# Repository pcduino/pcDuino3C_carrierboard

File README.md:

# pcDuino3C_carrierboard
This is the fully open source pcDuino3C carrierboard design files

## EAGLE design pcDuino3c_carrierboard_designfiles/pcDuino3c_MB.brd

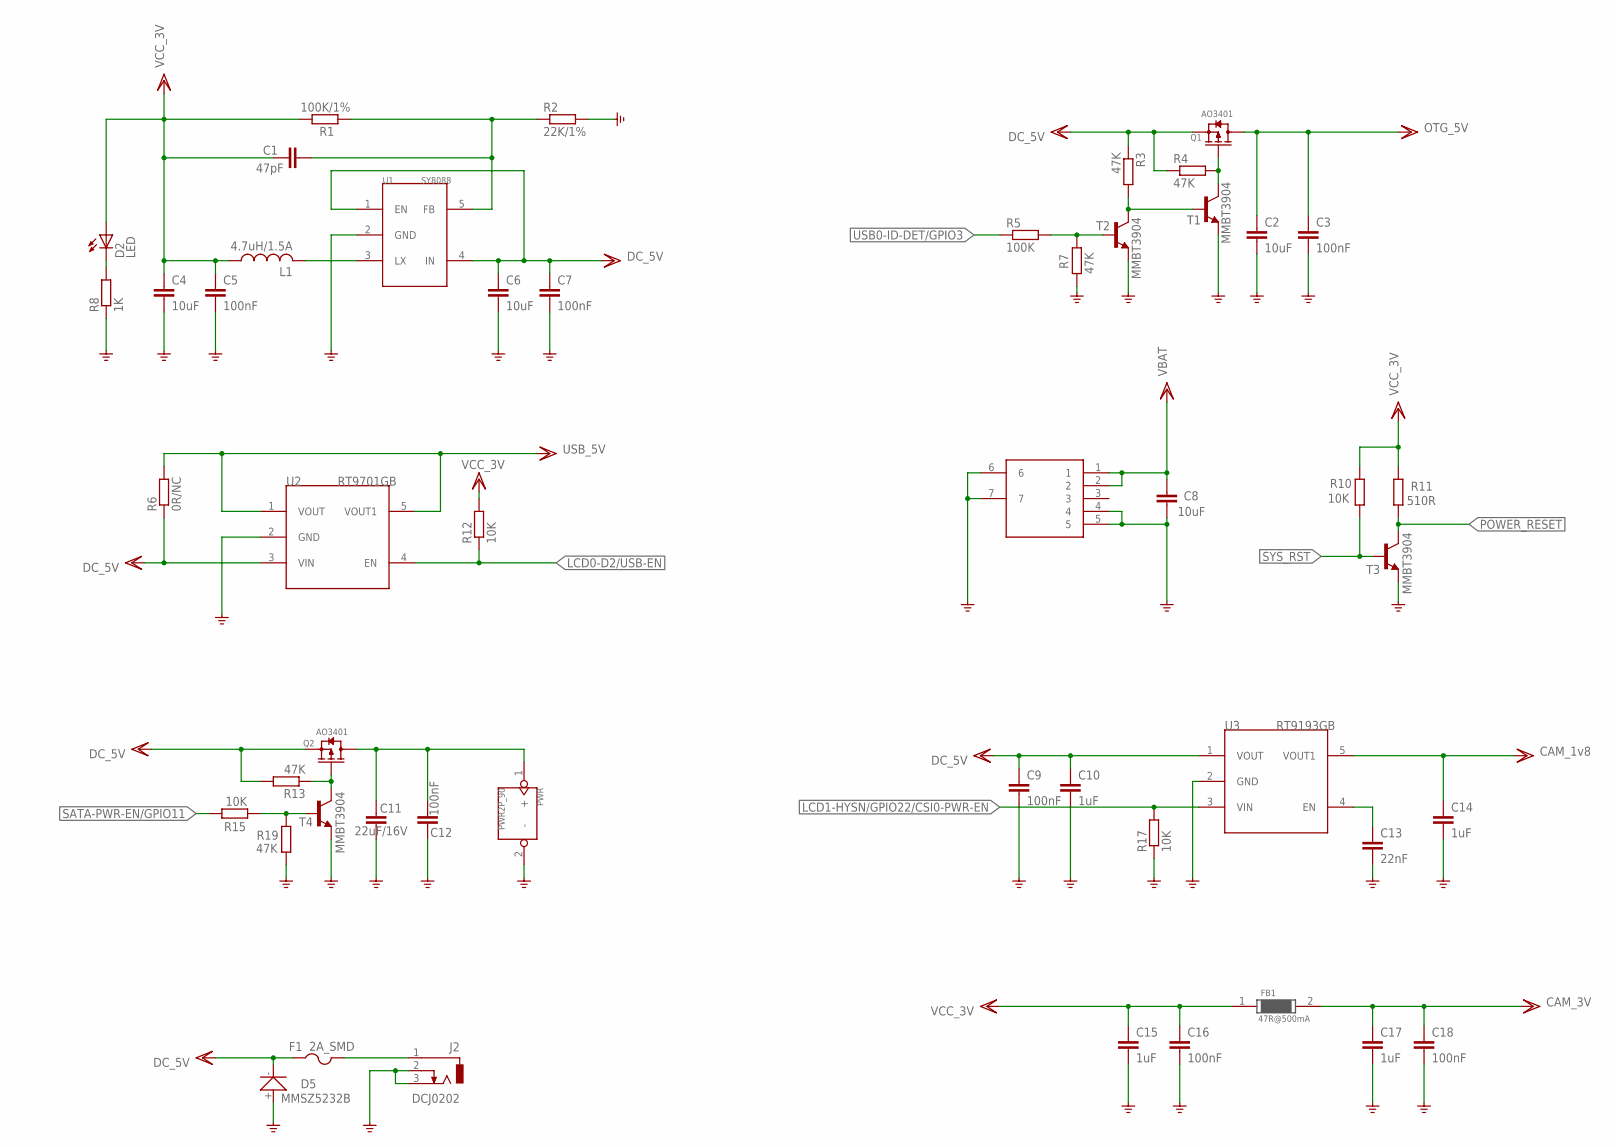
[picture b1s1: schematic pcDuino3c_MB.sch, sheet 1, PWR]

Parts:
C1: 47pF; C0402K
C2, C4, C6, C8: 10uF; C0805
C3, C5, C7, C12, C16, C18: 100nF; C0402K
C9: 100nF; C0805
C10, C14: 1uF; C0402K
C11: 22uF/16V; C0805
C13: 22nF; C0402K
C15, C17: 1uF; C0805
D2: LED; CHIP-LED-0805
D5: MMSZ5232B; SOD123
F1: 2A_SMD; R1206
FB1: 47R@500mA; R0603
J1: CON-BAT; CON-BAT-5P-1MM
J2: DCJ0202
L1: 4.7uH/1.5A; L_CD32
PWR: PWR2P_90; PWR2P_2.54
Q1, Q2: AO3401; SOT23
R1: 100K/1%; R0402
R2: 22K/1%; R0402
R3, R4, R7, R13, R19: 47K; R0402
R5: 100K; R0402
R6: 0R/NC; R0402
R8: 1K; R0402
R10, R12, R15, R17: 10K; R0402
R11: 510R; R0402
T1, T2, T3, T4: MMBT3904; SOT23-BEC
U1: SY8088; SOT23-5
U2: RT9701GB; SOT23-5
U3: RT9193GB; SOT23-5

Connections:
CAM_1V8: C14.1, U3.5 (VOUT1); also elsewhere on the board
CAM_3V: C17.1, C18.1, FB1.2; also elsewhere on the board
DC_5V: C6.1, C7.1, C9.1, C10.1, D5.-, F1.1, Q1.2 (S), Q2.2 (S), R3.1, R4.1, R6.1, R13.2, U1.1 (EN), U1.4 (IN), U2.3 (VIN), U3.1 (VOUT); also elsewhere on the board
GND: C2.2, C3.2, C4.2, C5.2, C6.2, C7.2, C8.2, C9.2, C10.2, C11.2, C12.2, C13.2, C14.2, C15.2, C16.2, C17.2, C18.2, D5.+, J1.4, J1.5, J1.6, J1.7, J2.2, J2.3, PWR.2 (-), R2.2, R7.1, R8.1, R17.1, R19.1, T1.E, T2.E, T3.E, T4.E, U1.2 (GND), U2.2 (GND), U3.2 (GND); also elsewhere on the board
LCD0-D2/USB-EN: R12.1, U2.4 (EN); also elsewhere on the board
LCD1-HYSN/GPIO22/CSI0-PWR-EN: R17.2, U3.3 (VIN)
unnamed: C13.1, U3.4 (EN)
unnamed: L1.2, U1.3 (LX)
unnamed: C1.2, R1.1, R2.1, U1.5 (FB)
unnamed: D2.C, R8.2
unnamed: Q1.1 (G), R4.2, T1.C
unnamed: R3.2, T1.B, T2.C
unnamed: R5.2, R7.2, T2.B
unnamed: C11.1, C12.1, PWR.1 (+), Q2.3 (D)
unnamed: F1.2, J2.1
unnamed: Q2.1 (G), R13.1, T4.C
unnamed: R15.1, R19.2, T4.B
OTG_5V: C2.1, C3.1, Q1.3 (D); also elsewhere on the board
POWER_RESET: R11.1, T3.C; also elsewhere on the board
SATA-PWR-EN/GPIO11: R15.2; also elsewhere on the board
SYS_RST: R10.1, T3.B; also elsewhere on the board
USB0-ID-DET/GPIO3: R5.1; also elsewhere on the board
USB_5V: R6.2, U2.1 (VOUT), U2.5 (VOUT1); also elsewhere on the board
VBAT: C8.1, J1.1, J1.2; also elsewhere on the board
VCC_3V: C1.1, C4.1, C5.1, C15.1, C16.1, D2.A, FB1.1, L1.1, R1.2, R10.2, R11.2, R12.2; also elsewhere on the board

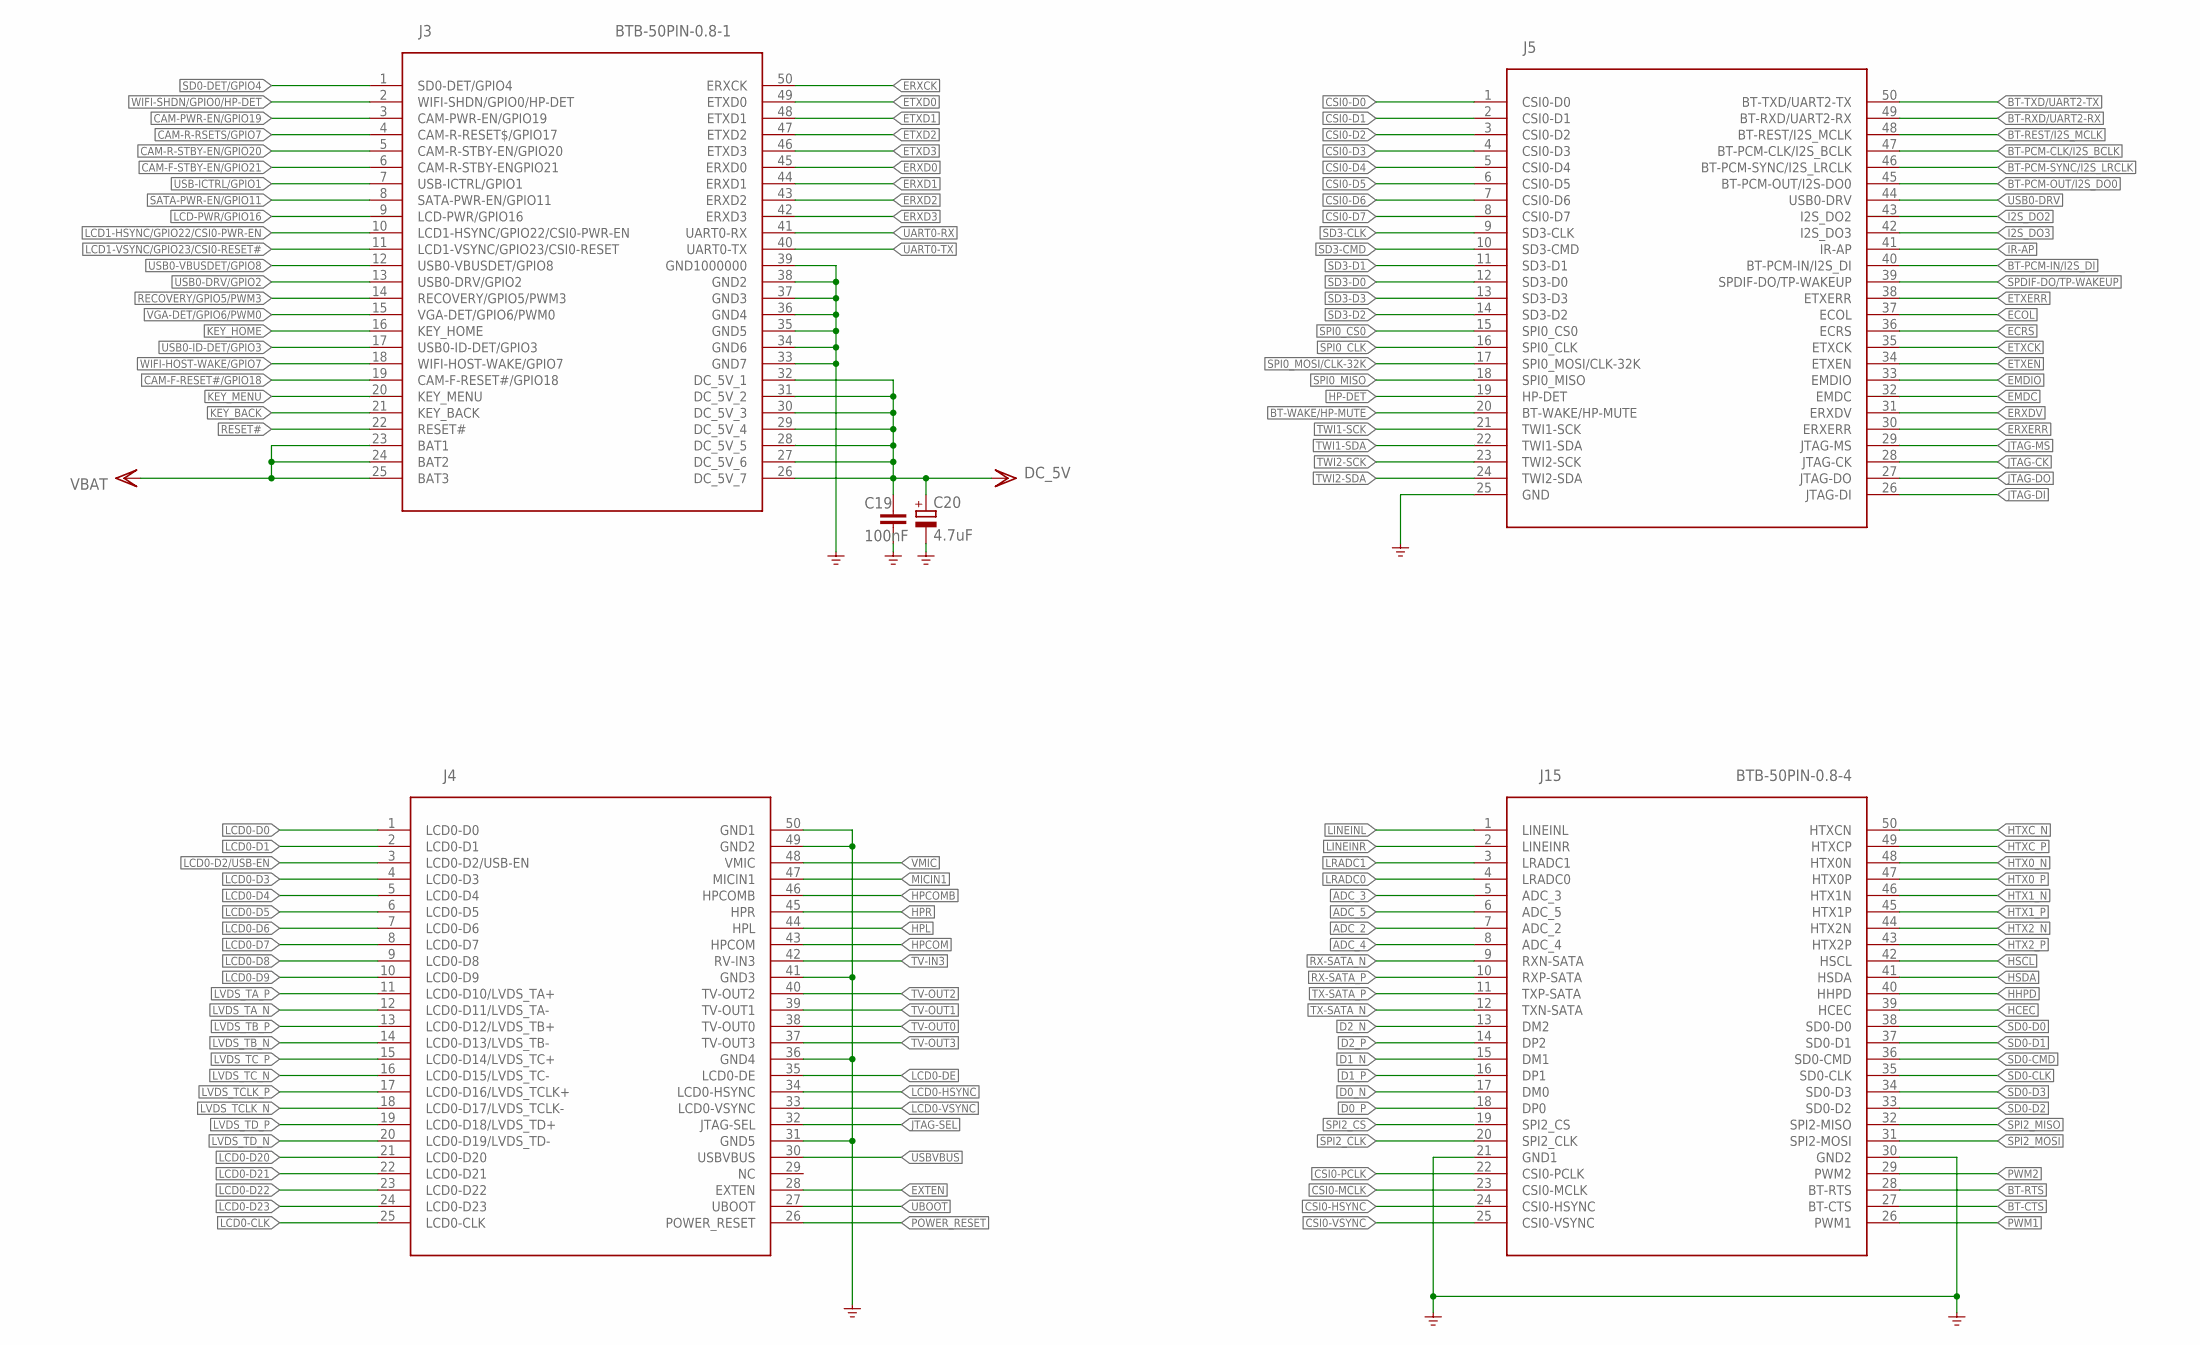
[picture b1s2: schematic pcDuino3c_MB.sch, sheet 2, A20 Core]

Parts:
C19: 100nF; C0402K
C20: 4.7uF; CT7343
J3: BTB-50PIN-0.8-1; BTB-50PIN-0.8
J4: BTB-50PIN-0.8-3; BTB-50PIN-0.8
J5: BTB-50PIN-0.8-2; BTB-50PIN-0.8
J15: BTB-50PIN-0.8-4; BTB-50PIN-0.8

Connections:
ADC_2: J15.7 (ADC_2); also elsewhere on the board
ADC_3: J15.5 (ADC_3); also elsewhere on the board
ADC_4: J15.8 (ADC_4); also elsewhere on the board
ADC_5: J15.6 (ADC_5); also elsewhere on the board
BT-CTS: J15.27 (BT-CTS)
BT-PCM-CLK/I2S_BCLK: J5.47 (BT-PCM-CLK/I2S_BCLK)
BT-PCM-IN/I2S_DI: J5.40 (BT-PCM-IN/I2S_DI)
BT-PCM-OUT/I2S_DO0: J5.45 (BT-PCM-OUT/I2S-DO0)
BT-PCM-SYNC/I2S_LRCLK: J5.46 (BT-PCM-SYNC/I2S_LRCLK)
BT-REST/I2S_MCLK: J5.48 (BT-REST/I2S_MCLK)
BT-RTS: J15.28 (BT-RTS)
BT-RXD/UART2-RX: J5.49 (BT-RXD/UART2-RX); also elsewhere on the board
BT-TXD/UART2-TX: J5.50 (BT-TXD/UART2-TX); also elsewhere on the board
BT-WAKE/HP-MUTE: J5.20 (BT-WAKE/HP-MUTE)
CAM-F-RESET#/GPIO18: J3.19 (CAM-F-RESET#/GPIO18); also elsewhere on the board
CAM-F-STBY-EN/GPIO21: J3.6 (CAM-R-STBY-ENGPIO21); also elsewhere on the board
CAM-PWR-EN/GPIO19: J3.3 (CAM-PWR-EN/GPIO19); also elsewhere on the board
CAM-R-RSETS/GPIO7: J3.4 (CAM-R-RESET$/GPIO17)
CAM-R-STBY-EN/GPIO20: J3.5 (CAM-R-STBY-EN/GPIO20); also elsewhere on the board
CSI0-D0: J5.1 (CSI0-D0); also elsewhere on the board
CSI0-D1: J5.2 (CSI0-D1); also elsewhere on the board
CSI0-D2: J5.3 (CSI0-D2); also elsewhere on the board
CSI0-D3: J5.4 (CSI0-D3); also elsewhere on the board
CSI0-D4: J5.5 (CSI0-D4); also elsewhere on the board
CSI0-D5: J5.6 (CSI0-D5); also elsewhere on the board
CSI0-D6: J5.7 (CSI0-D6); also elsewhere on the board
CSI0-D7: J5.8 (CSI0-D7); also elsewhere on the board
CSI0-HSYNC: J15.24 (CSI0-HSYNC); also elsewhere on the board
CSI0-MCLK: J15.23 (CSI0-MCLK); also elsewhere on the board
CSI0-PCLK: J15.22 (CSI0-PCLK); also elsewhere on the board
CSI0-VSYNC: J15.25 (CSI0-VSYNC); also elsewhere on the board
D0_N: J15.17 (DM0); also elsewhere on the board
D0_P: J15.18 (DP0); also elsewhere on the board
D1_N: J15.15 (DM1); also elsewhere on the board
D1_P: J15.16 (DP1); also elsewhere on the board
D2_N: J15.13 (DM2); also elsewhere on the board
D2_P: J15.14 (DP2); also elsewhere on the board
DC_5V: C19.1, C20.+, J3.26 (DC_5V_7), J3.27 (DC_5V_6), J3.28 (DC_5V_5), J3.29 (DC_5V_4), J3.30 (DC_5V_3), J3.31 (DC_5V_2), J3.32 (DC_5V_1); also elsewhere on the board
ECOL: J5.37 (ECOL); also elsewhere on the board
ECRS: J5.36 (ECRS); also elsewhere on the board
EMDC: J5.32 (EMDC); also elsewhere on the board
EMDIO: J5.33 (EMDIO); also elsewhere on the board
ERXCK: J3.50 (ERXCK); also elsewhere on the board
ERXD0: J3.45 (ERXD0); also elsewhere on the board
ERXD1: J3.44 (ERXD1); also elsewhere on the board
ERXD2: J3.43 (ERXD2); also elsewhere on the board
ERXD3: J3.42 (ERXD3); also elsewhere on the board
ERXDV: J5.31 (ERXDV); also elsewhere on the board
ERXERR: J5.30 (ERXERR); also elsewhere on the board
ETXCK: J5.35 (ETXCK); also elsewhere on the board
ETXD0: J3.49 (ETXD0); also elsewhere on the board
ETXD1: J3.48 (ETXD1); also elsewhere on the board
ETXD2: J3.47 (ETXD2); also elsewhere on the board
ETXD3: J3.46 (ETXD3); also elsewhere on the board
ETXEN: J5.34 (ETXEN); also elsewhere on the board
ETXERR: J5.38 (ETXERR); also elsewhere on the board
EXTEN: J4.28 (EXTEN)
GND: C19.2, C20.-, J3.33 (GND7), J3.34 (GND6), J3.35 (GND5), J3.36 (GND4), J3.37 (GND3), J3.38 (GND2), J3.39 (GND1000000), J4.31 (GND5), J4.36 (GND4), J4.41 (GND3), J4.49 (GND2), J4.50 (GND1), J5.25 (GND), J15.21 (GND1), J15.30 (GND2); also elsewhere on the board
HCEC: J15.39 (HCEC); also elsewhere on the board
HHPD: J15.40 (HHPD); also elsewhere on the board
HP-DET: J5.19 (HP-DET)
HPCOM: J4.43 (HPCOM); also elsewhere on the board
HPCOMB: J4.46 (HPCOMB); also elsewhere on the board
HPL: J4.44 (HPL); also elsewhere on the board
HPR: J4.45 (HPR); also elsewhere on the board
HSCL: J15.42 (HSCL); also elsewhere on the board
HSDA: J15.41 (HSDA); also elsewhere on the board
HTX0_N: J15.48 (HTX0N); also elsewhere on the board
HTX0_P: J15.47 (HTX0P); also elsewhere on the board
HTX1_N: J15.46 (HTX1N); also elsewhere on the board
HTX1_P: J15.45 (HTX1P); also elsewhere on the board
HTX2_N: J15.44 (HTX2N); also elsewhere on the board
HTX2_P: J15.43 (HTX2P); also elsewhere on the board
HTXC_N: J15.50 (HTXCN); also elsewhere on the board
HTXC_P: J15.49 (HTXCP); also elsewhere on the board
I2S_DO2: J5.43 (I2S_DO2)
I2S_DO3: J5.42 (I2S_DO3)
IR-AP: J5.41 (IR-AP); also elsewhere on the board
JTAG-CK: J5.28 (JTAG-CK)
JTAG-DI: J5.26 (JTAG-DI)
JTAG-DO: J5.27 (JTAG-DO)
JTAG-MS: J5.29 (JTAG-MS)
JTAG-SEL: J4.32 (JTAG-SEL)
KEY_BACK: J3.21 (KEY_BACK); also elsewhere on the board
KEY_HOME: J3.16 (KEY_HOME); also elsewhere on the board
KEY_MENU: J3.20 (KEY_MENU); also elsewhere on the board
LCD0-CLK: J4.25 (LCD0-CLK)
LCD0-D0: J4.1 (LCD0-D0)
LCD0-D1: J4.2 (LCD0-D1)
LCD0-D2/USB-EN: J4.3 (LCD0-D2/USB-EN); also elsewhere on the board
LCD0-D3: J4.4 (LCD0-D3)
LCD0-D4: J4.5 (LCD0-D4)
LCD0-D5: J4.6 (LCD0-D5)
LCD0-D6: J4.7 (LCD0-D6)
LCD0-D7: J4.8 (LCD0-D7)
LCD0-D8: J4.9 (LCD0-D8)
LCD0-D9: J4.10 (LCD0-D9)
LCD0-D20: J4.21 (LCD0-D20)
LCD0-D21: J4.22 (LCD0-D21)
LCD0-D22: J4.23 (LCD0-D22)
LCD0-D23: J4.24 (LCD0-D23)
LCD0-DE: J4.35 (LCD0-DE)
LCD0-HSYNC: J4.34 (LCD0-HSYNC)
LCD0-VSYNC: J4.33 (LCD0-VSYNC)
LCD1-HSYNC/GPIO22/CSI0-PWR-EN: J3.10 (LCD1-HSYNC/GPIO22/CSI0-PWR-EN); also elsewhere on the board
LCD1-VSYNC/GPIO23/CSI0-RESET#: J3.11 (LCD1-VSYNC/GPIO23/CSI0-RESET); also elsewhere on the board
LCD-PWR/GPIO16: J3.9 (LCD-PWR/GPIO16)
LINEINL: J15.1 (LINEINL)
LINEINR: J15.2 (LINEINR)
LRADC0: J15.4 (LRADC0); also elsewhere on the board
LRADC1: J15.3 (LRADC1); also elsewhere on the board
LVDS_TA_N: J4.12 (LCD0-D11/LVDS_TA-); also elsewhere on the board
LVDS_TA_P: J4.11 (LCD0-D10/LVDS_TA+); also elsewhere on the board
LVDS_TB_N: J4.14 (LCD0-D13/LVDS_TB-); also elsewhere on the board
LVDS_TB_P: J4.13 (LCD0-D12/LVDS_TB+); also elsewhere on the board
LVDS_TCLK_N: J4.18 (LCD0-D17/LVDS_TCLK-); also elsewhere on the board
LVDS_TCLK_P: J4.17 (LCD0-D16/LVDS_TCLK+); also elsewhere on the board
LVDS_TC_N: J4.16 (LCD0-D15/LVDS_TC-); also elsewhere on the board
LVDS_TC_P: J4.15 (LCD0-D14/LVDS_TC+); also elsewhere on the board
LVDS_TD_N: J4.20 (LCD0-D19/LVDS_TD-); also elsewhere on the board
LVDS_TD_P: J4.19 (LCD0-D18/LVDS_TD+); also elsewhere on the board
MICIN1: J4.47 (MICIN1); also elsewhere on the board
POWER_RESET: J4.26 (POWER_RESET); also elsewhere on the board
PWM1: J15.26 (PWM1); also elsewhere on the board
PWM2: J15.29 (PWM2); also elsewhere on the board
RECOVERY/GPIO5/PWM3: J3.14 (RECOVERY/GPIO5/PWM3); also elsewhere on the board
RESET#: J3.22 (RESET#)
RX-SATA_N: J15.9 (RXN-SATA); also elsewhere on the board
RX-SATA_P: J15.10 (RXP-SATA); also elsewhere on the board
SATA-PWR-EN/GPIO11: J3.8 (SATA-PWR-EN/GPIO11); also elsewhere on the board
SD0-CLK: J15.35 (SD0-CLK); also elsewhere on the board
SD0-CMD: J15.36 (SD0-CMD); also elsewhere on the board
SD0-D0: J15.38 (SD0-D0); also elsewhere on the board
SD0-D1: J15.37 (SD0-D1); also elsewhere on the board
SD0-D2: J15.33 (SD0-D2); also elsewhere on the board
SD0-D3: J15.34 (SD0-D3); also elsewhere on the board
SD0-DET/GPIO4: J3.1 (SD0-DET/GPIO4); also elsewhere on the board
SD3-CLK: J5.9 (SD3-CLK)
SD3-CMD: J5.10 (SD3-CMD)
SD3-D0: J5.12 (SD3-D0)
SD3-D1: J5.11 (SD3-D1)
SD3-D2: J5.14 (SD3-D2)
SD3-D3: J5.13 (SD3-D3)
SPDIF-DO/TP-WAKEUP: J5.39 (SPDIF-DO/TP-WAKEUP)
SPI0_CLK: J5.16 (SPI0_CLK); also elsewhere on the board
SPI0_CS0: J5.15 (SPI0_CS0); also elsewhere on the board
SPI0_MISO: J5.18 (SPI0_MISO); also elsewhere on the board
SPI0_MOSI/CLK-32K: J5.17 (SPI0_MOSI/CLK-32K); also elsewhere on the board
SPI2_CLK: J15.20 (SPI2_CLK)
SPI2_CS: J15.19 (SPI2_CS)
SPI2_MISO: J15.32 (SPI2-MISO)
SPI2_MOSI: J15.31 (SPI2-MOSI)
TV-IN3: J4.42 (RV-IN3)
TV-OUT0: J4.38 (TV-OUT0)
TV-OUT1: J4.39 (TV-OUT1)
TV-OUT2: J4.40 (TV-OUT2)
TV-OUT3: J4.37 (TV-OUT3)
TWI1-SCK: J5.21 (TWI1-SCK); also elsewhere on the board
TWI1-SDA: J5.22 (TWI1-SDA); also elsewhere on the board
TWI2-SCK: J5.23 (TWI2-SCK); also elsewhere on the board
TWI2-SDA: J5.24 (TWI2-SDA); also elsewhere on the board
TX-SATA_N: J15.12 (TXN-SATA); also elsewhere on the board
TX-SATA_P: J15.11 (TXP-SATA); also elsewhere on the board
UART0-RX: J3.41 (UART0-RX); also elsewhere on the board
UART0-TX: J3.40 (UART0-TX); also elsewhere on the board
UBOOT: J4.27 (UBOOT); also elsewhere on the board
USB0-DRV: J5.44 (USB0-DRV)
USB0-DRV/GPIO2: J3.13 (USB0-DRV/GPIO2); also elsewhere on the board
USB0-ID-DET/GPIO3: J3.17 (USB0-ID-DET/GPIO3); also elsewhere on the board
USB0-VBUSDET/GPIO8: J3.12 (USB0-VBUSDET/GPIO8); also elsewhere on the board
USB-ICTRL/GPIO1: J3.7 (USB-ICTRL/GPIO1); also elsewhere on the board
USBVBUS: J4.30 (USBVBUS)
VBAT: J3.23 (BAT1), J3.24 (BAT2), J3.25 (BAT3); also elsewhere on the board
VGA-DET/GPIO6/PWM0: J3.15 (VGA-DET/GPIO6/PWM0); also elsewhere on the board
VMIC: J4.48 (VMIC); also elsewhere on the board
WIFI-HOST-WAKE/GPIO7: J3.18 (WIFI-HOST-WAKE/GPIO7); also elsewhere on the board
WIFI-SHDN/GPIO0/HP-DET: J3.2 (WIFI-SHDN/GPIO0/HP-DET); also elsewhere on the board

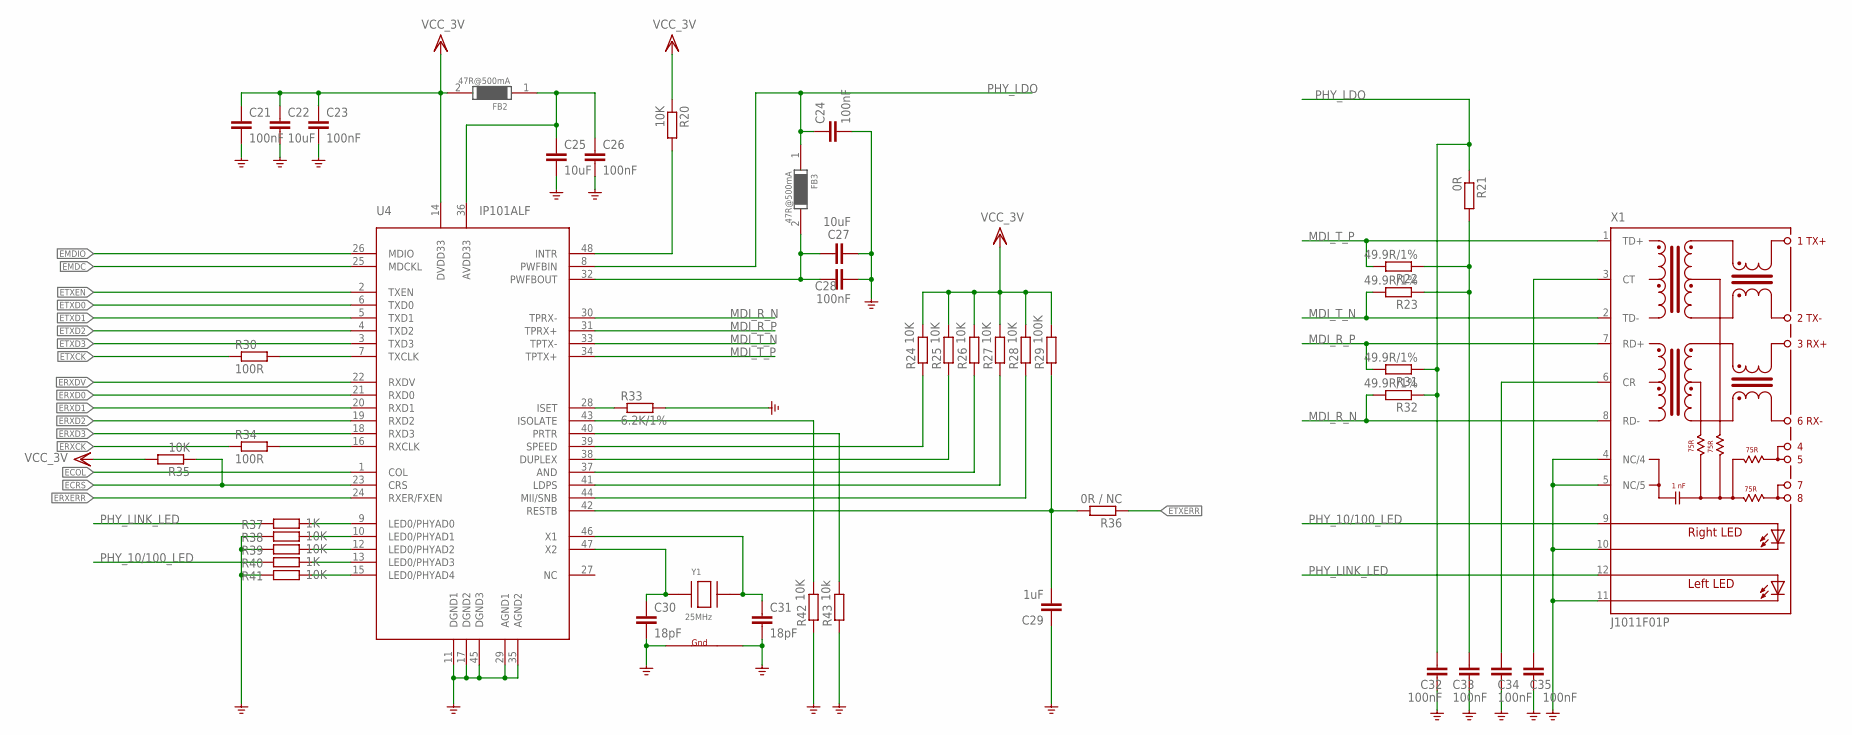
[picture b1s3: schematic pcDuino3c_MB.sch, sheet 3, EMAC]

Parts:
C21, C23, C24, C26, C28, C32, C33, C34, C35: 100nF; C0402K
C22, C25, C27: 10uF; C0805
C29: 1uF; C0402K
C30, C31: 18pF; C0402K
FB2, FB3: 47R@500mA; R0603
R20, R24, R25, R26, R27, R28, R35, R38, R39, R41, R42: 10K; R0402
R21: 0R; R0402
R22, R23, R31, R32: 49.9R/1%; R0402
R29: 100K; R0402
R30, R34: 100R; R0402
R33: 6.2K/1%; R0402
R36: 0R / NC; R0402
R37, R40: 1K; R0402
R43: 10k; R0402
U4: IP101ALF; LQFP48-7X7
X1: J1011F01P; J1
Y1: 25MHz; NX3225

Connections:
ECOL: U4.1 (COL); also elsewhere on the board
ECRS: R35.1, U4.23 (CRS); also elsewhere on the board
EMDC: U4.25 (MDCKL); also elsewhere on the board
EMDIO: U4.26 (MDIO); also elsewhere on the board
ERXCK: R34.1; also elsewhere on the board
ERXD0: U4.21 (RXD0); also elsewhere on the board
ERXD1: U4.20 (RXD1); also elsewhere on the board
ERXD2: U4.19 (RXD2); also elsewhere on the board
ERXD3: U4.18 (RXD3); also elsewhere on the board
ERXDV: U4.22 (RXDV); also elsewhere on the board
ERXERR: U4.24 (RXER/FXEN); also elsewhere on the board
ETXCK: R30.1; also elsewhere on the board
ETXD0: U4.6 (TXD0); also elsewhere on the board
ETXD1: U4.5 (TXD1); also elsewhere on the board
ETXD2: U4.4 (TXD2); also elsewhere on the board
ETXD3: U4.3 (TXD3); also elsewhere on the board
ETXEN: U4.2 (TXEN); also elsewhere on the board
ETXERR: R36.1; also elsewhere on the board
GND: C21.2, C22.2, C23.2, C24.2, C25.2, C26.2, C27.1, C28.2, C29.1, C30.2, C31.2, C32.1, C33.1, C34.1, C35.1, R33.2, R38.1, R39.1, R41.1, R42.1, R43.1, U4.11 (DGND1), U4.17 (DGND2), U4.29 (AGND1), U4.35 (AGND2), U4.45 (DGND3), X1.4 (NC/4), X1.5 (NC/5), X1.10 (C-R), X1.11 (C-L), Y1.2 (G1), Y1.4 (G2); also elsewhere on the board
MDI_R_N: R32.2, U4.30 (TPRX-), X1.8 (RD-)
MDI_R_P: R31.2, U4.31 (TPRX+), X1.7 (RD+)
MDI_T_N: R23.2, U4.33 (TPTX-), X1.2 (TD-)
MDI_T_P: R22.2, U4.34 (TPTX+), X1.1 (TD+)
unnamed: C25.1, C26.1, FB2.1, U4.36 (AVDD33)
unnamed: C34.2, X1.6 (CR)
unnamed: C35.2, X1.3 (CT)
unnamed: C33.2, R21.2, R22.1, R23.1
unnamed: R20.2, U4.48 (INTR)
unnamed: C27.2, C28.1, FB3.2, U4.32 (PWFBOUT)
unnamed: R33.1, U4.28 (ISET)
unnamed: R37.2, U4.9 (LED0/PHYAD0)
unnamed: R38.2, U4.10 (LED0/PHYAD1)
unnamed: R39.2, U4.12 (LED0/PHYAD2)
unnamed: R40.2, U4.13 (LED0/PHYAD3)
unnamed: R41.2, U4.15 (LED0/PHYAD4)
unnamed: C30.1, U4.47 (X2), Y1.1 (X1)
unnamed: R34.2, U4.16 (RXCLK)
unnamed: R30.2, U4.7 (TXCLK)
unnamed: C31.1, U4.46 (X1), Y1.3 (X2)
unnamed: R27.1, U4.41 (LDPS)
unnamed: R42.2, U4.43 (ISOLATE)
unnamed: R43.2, U4.40 (PRTR)
unnamed: R24.1, U4.39 (SPEED)
unnamed: R25.1, U4.38 (DUPLEX)
unnamed: R26.1, U4.37 (AND)
unnamed: R28.1, U4.44 (MII/SNB)
unnamed: C29.2, R29.1, R36.2, U4.42 (RESTB)
PHY_10/100_LED: R40.1, X1.9 (A-R)
PHY_LDO: C24.1, C32.2, FB3.1, R21.1, R31.1, R32.1, U4.8 (PWFBIN)
PHY_LINK_LED: R37.1, X1.12 (AL)
VCC_3V: C21.1, C22.1, C23.1, FB2.2, R20.1, R24.2, R25.2, R26.2, R27.2, R28.2, R29.2, R35.2, U4.14 (DVDD33); also elsewhere on the board

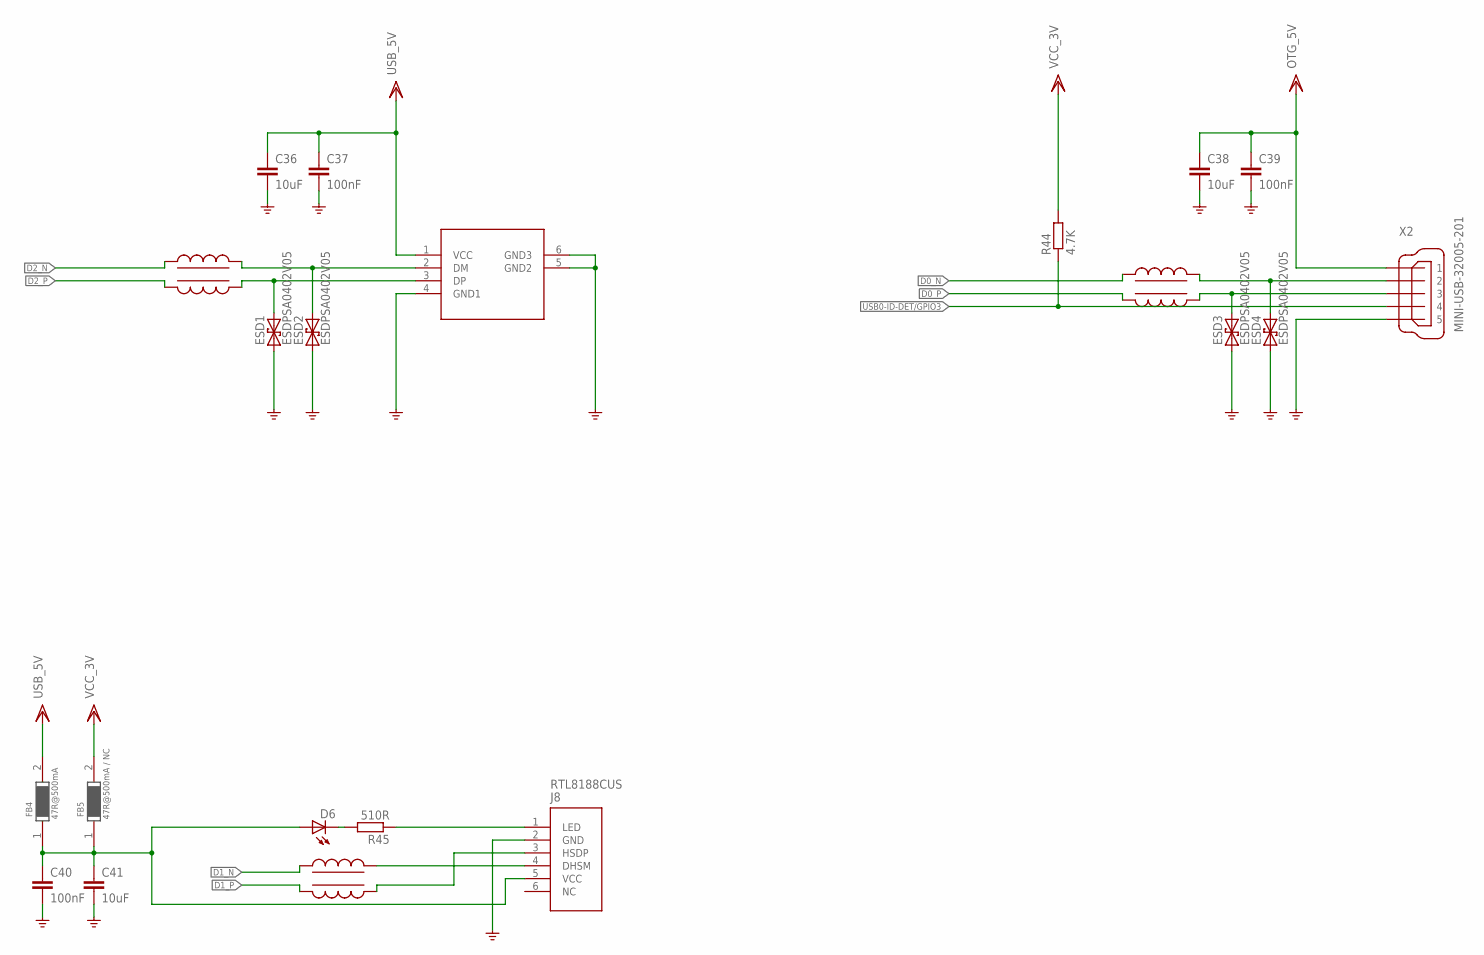
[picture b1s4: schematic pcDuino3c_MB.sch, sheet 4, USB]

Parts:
C36, C38: 10uF; C0805
C37, C39: 100nF; C0402K
C40: 100nF; C0805
C41: 10uF; C0402K
D6: LED; CHIP-LED-0805
ESD1, ESD2, ESD3, ESD4: ESDPSA0402V05; R0402
FB4: 47R@500mA; R0603
FB5: 47R@500mA / NC; R0603
J7: CON-USB
J8: RTL8188CUS; PCDUINO-WIFI-0_1PRIMARY
L2, L3, L4: IND-CL-2M2012; CL-2M2012
R44: 4.7K; R0402
R45: 510R; R0402
X2: MINI-USB-32005-201; 32005-201

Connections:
D0_N: L3.1; also elsewhere on the board
D0_P: L3.2; also elsewhere on the board
D1_N: L4.1; also elsewhere on the board
D1_P: L4.2; also elsewhere on the board
D2_N: L2.1; also elsewhere on the board
D2_P: L2.2; also elsewhere on the board
GND: C36.2, C37.2, C38.2, C39.2, C40.2, C41.2, ESD1.1, ESD2.1, ESD3.1, ESD4.1, J7.4 (GND1), J7.5 (GND2), J7.6 (GND3), J8.2 (GND), X2.5; also elsewhere on the board
unnamed: J8.4 (DHSM), L4.4
unnamed: J8.1 (LED), R45.1
unnamed: J8.3 (HSDP), L4.3
unnamed: D6.C, R45.2
unnamed: ESD2.2, J7.2 (DM), L2.4
unnamed: ESD1.2, J7.3 (DP), L2.3
unnamed: ESD4.2, L3.4, X2.2
unnamed: C40.1, C41.1, D6.A, FB4.1, FB5.1, J8.5 (VCC)
unnamed: ESD3.2, L3.3, X2.3
OTG_5V: C38.1, C39.1, X2.1; also elsewhere on the board
USB0-ID-DET/GPIO3: R44.1, X2.4; also elsewhere on the board
USB_5V: C36.1, C37.1, FB4.2, J7.1 (VCC); also elsewhere on the board
VCC_3V: FB5.2, R44.2; also elsewhere on the board

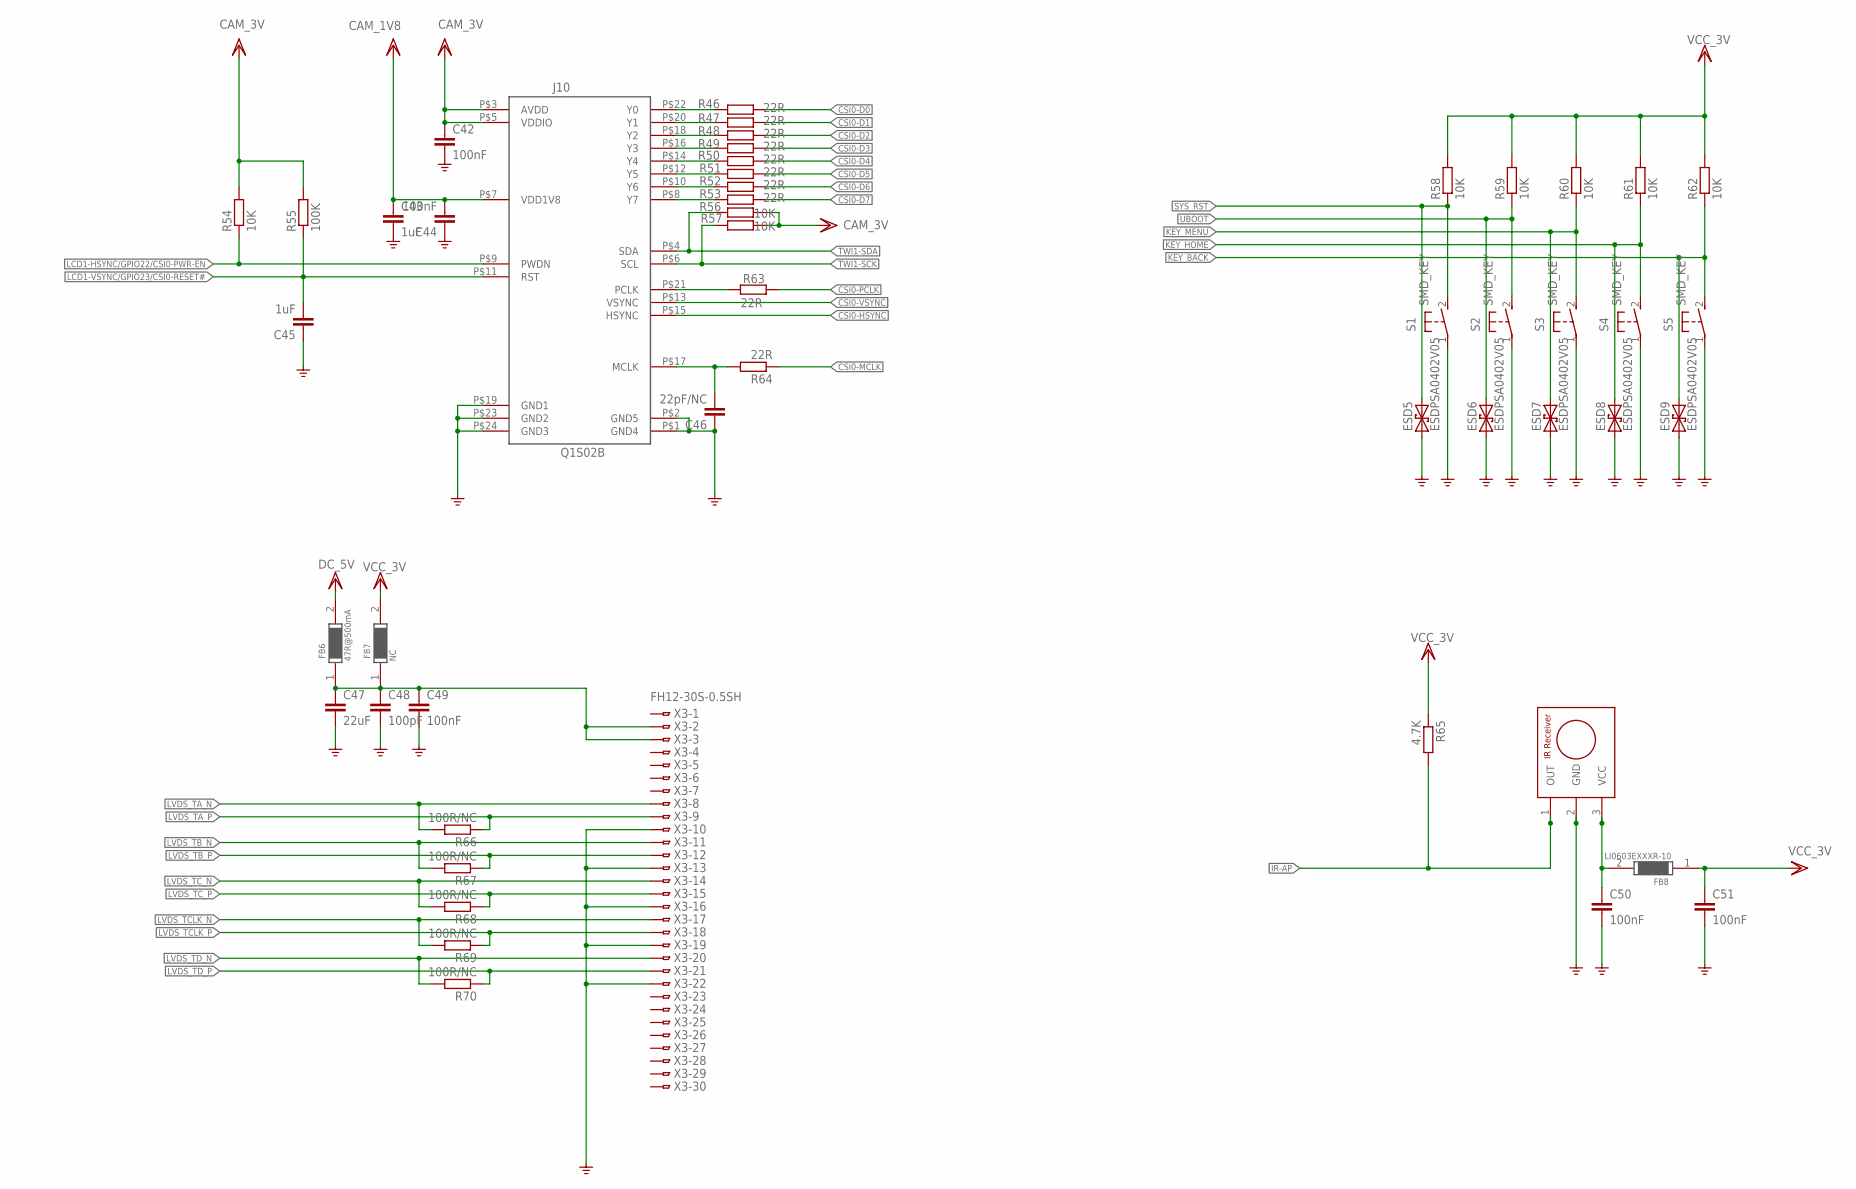
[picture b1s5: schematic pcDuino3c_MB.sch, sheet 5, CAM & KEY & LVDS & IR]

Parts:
C42, C44, C51: 100nF; C0402K
C43: 1uF; C0805
C45: 1uF; C0402K
C46: 22pF/NC; C0402K
C47: 22uF; C0805
C48: 100pF; C0402K
C49, C50: 100nF; C0805
ESD5, ESD6, ESD7, ESD8, ESD9: ESDPSA0402V05; R0402
FB6: 47R@500mA; R0603
FB7: NC; R0603
FB8: LI0603EXXXR-10; R0603
J10: Q1S02B; AXK824145WG
R46, R47, R48, R49, R50, R51, R52, R53, R63, R64: 22R; R0402
R54, R56, R57, R58, R59, R60, R61, R62: 10K; R0402
R55: 100K; R0402
R65: 4.7K; R0402
R66, R67, R68, R69, R70: 100R/NC; R0402
S1, S2, S3, S4, S5: SMD_KEY; KEY
U9: INFARED; HS/VS1838
X3: FH12-30S-0.5SH

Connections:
CAM_1V8: C43.1, C44.2, J10.P$7 (VDD1V8); also elsewhere on the board
CAM_3V: C42.1, J10.P$3 (AVDD), J10.P$5 (VDDIO), R54.2, R55.2, R56.1, R57.1; also elsewhere on the board
CSI0-D0: R46.1; also elsewhere on the board
CSI0-D1: R47.1; also elsewhere on the board
CSI0-D2: R48.1; also elsewhere on the board
CSI0-D3: R49.1; also elsewhere on the board
CSI0-D4: R50.1; also elsewhere on the board
CSI0-D5: R51.1; also elsewhere on the board
CSI0-D6: R52.1; also elsewhere on the board
CSI0-D7: R53.1; also elsewhere on the board
CSI0-HSYNC: J10.P$15 (HSYNC); also elsewhere on the board
CSI0-MCLK: R64.1; also elsewhere on the board
CSI0-PCLK: R63.1; also elsewhere on the board
CSI0-VSYNC: J10.P$13 (VSYNC); also elsewhere on the board
DC_5V: FB6.2; also elsewhere on the board
GND: C42.2, C43.2, C44.1, C45.1, C46.1, C47.2, C48.2, C49.2, C50.2, C51.2, ESD5.1, ESD6.1, ESD7.1, ESD8.1, ESD9.1, J10.P$1 (GND4), J10.P$2 (GND5), J10.P$19 (GND1), J10.P$23 (GND2), J10.P$24 (GND3), S1.1, S2.1, S3.1, S4.1, S5.1, U9.2 (GND), X3.9, X3.12, X3.15, X3.18, X3.21; also elsewhere on the board
IR-AP: R65.2, U9.1 (OUT); also elsewhere on the board
KEY_BACK: ESD9.2, R62.1, S5.2 (S); also elsewhere on the board
KEY_HOME: ESD8.2, R61.1, S4.2 (S); also elsewhere on the board
KEY_MENU: ESD7.2, R60.1, S3.2 (S); also elsewhere on the board
LCD1-HSYNC/GPIO22/CSI0-PWR-EN: J10.P$9 (PWDN), R54.1; also elsewhere on the board
LCD1-VSYNC/GPIO23/CSI0-RESET#: C45.2, J10.P$11 (RST), R55.1; also elsewhere on the board
LVDS_TA_N: R66.2, X3.23; also elsewhere on the board
LVDS_TA_P: R66.1, X3.22; also elsewhere on the board
LVDS_TB_N: R67.2, X3.20; also elsewhere on the board
LVDS_TB_P: R67.1, X3.19; also elsewhere on the board
LVDS_TCLK_N: R69.2, X3.14; also elsewhere on the board
LVDS_TCLK_P: R69.1, X3.13; also elsewhere on the board
LVDS_TC_N: R68.2, X3.17; also elsewhere on the board
LVDS_TC_P: R68.1, X3.16; also elsewhere on the board
LVDS_TD_N: R70.2, X3.11; also elsewhere on the board
LVDS_TD_P: R70.1, X3.10; also elsewhere on the board
unnamed: J10.P$22 (Y0), R46.2
unnamed: J10.P$20 (Y1), R47.2
unnamed: J10.P$18 (Y2), R48.2
unnamed: J10.P$16 (Y3), R49.2
unnamed: J10.P$14 (Y4), R50.2
unnamed: J10.P$12 (Y5), R51.2
unnamed: J10.P$10 (Y6), R52.2
unnamed: J10.P$8 (Y7), R53.2
unnamed: J10.P$21 (PCLK), R63.2
unnamed: C46.2, J10.P$17 (MCLK), R64.2
unnamed: C47.1, C48.1, C49.1, FB6.1, FB7.1, X3.28, X3.29
unnamed: C50.1, FB8.2, U9.3 (VCC)
SYS_RST: ESD5.2, R58.1, S1.2 (S); also elsewhere on the board
TWI1-SCK: J10.P$6 (SCL), R57.2; also elsewhere on the board
TWI1-SDA: J10.P$4 (SDA), R56.2; also elsewhere on the board
UBOOT: ESD6.2, R59.1, S2.2 (S); also elsewhere on the board
VCC_3V: C51.1, FB7.2, FB8.1, R58.2, R59.2, R60.2, R61.2, R62.2, R65.1; also elsewhere on the board
